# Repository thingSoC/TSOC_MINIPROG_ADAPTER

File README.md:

# TSOC_MINIPROG_ADAPTER

**TSOC_MINIPROG_ADAPTER** is a USB Serial, JTAG, and I2C programming adapter for thingSoc, 
and an example **thingSoC Reference Design.** 

[thingSoC](http://www.thingsoc.com) is an open source standard that defines a vendor 
independent socket system for the creation of new Internet Things with automatic configuration options. 
The [thingSoC](http://www.thingsoc.com) Default Programming Connector (DPC) is a sixteen(16) pin dual row type, with 254mm spacing,
and is compatible with what is refered to in the industry as the "FTDI Basic" connector. 
[thingSoC](http://www.thingsoc.com) supports a wide variety of programming interfaces, 
including JTAG/SWD, I2C, SPI, UART, and USB Serial, and the Default Programming Connector (DPC)
can support a number of simultaineous interfaces.

The **TSOC_MINIPROG_ADAPTER** facilitates the use of "FTDI" USB to UART Serial Adapters
like the [Sparkfun FTDI Basic Breakout](https://www.sparkfun.com/products/9873) for serial bootstrap programming.
The **TSOC_MINIPROG_ADAPTER** also facilitates the use of "MiniProg" programmers,
such as the [MiniProg3](http://www.cypress.com/documentation/development-kitsboards/cy8ckit-002-psoc-miniprog3-program-and-debug-kit), 
[MiniProg1](http://www.cypress.com/documentation/development-kitsboards/cy3217-miniprog1), and [PSoC3/4/5 KitProg](http://www.cypress.com/documentation/development-kitsboards/cy8ckit-059-psoc-5lp-prototyping-kit-onboard-programmer-and).

The **thingSoC Reference Designs** are example thingSoC implementations that implement
various reference and testing circuits for demonstrating the use of the thingSoC libraries.
These reference designs are complete designs and can also serve as starting templates for users to customize.

---------------------------------------

[ *TSOC_MINIPROG_ADAPTER Top*](https://github.com/thingSoC/) [ *TSOC_MINIPROG_ADAPTER Bottom*](https://github.com/thingSoC/)

* thingSoC Compliant Module
* thingSoC Default Programming Connector (thingSoc DPC)
* FTDI Connector Adapter
* Miniprog Connector Adapter
* ISSP/I2C Programmer Adapter

---------------------------------------

## Documentation Index <a name="documentation_index"/>

[thingSoC Organization Website](http://thingSoC.github.io)

[thingSoC FAQ - Frequently Asked Questions](http://thingsoc.github.io/support/faq.html)

---------------------------------------

[  
*thingSoC*](http://thingsoc.github.io)

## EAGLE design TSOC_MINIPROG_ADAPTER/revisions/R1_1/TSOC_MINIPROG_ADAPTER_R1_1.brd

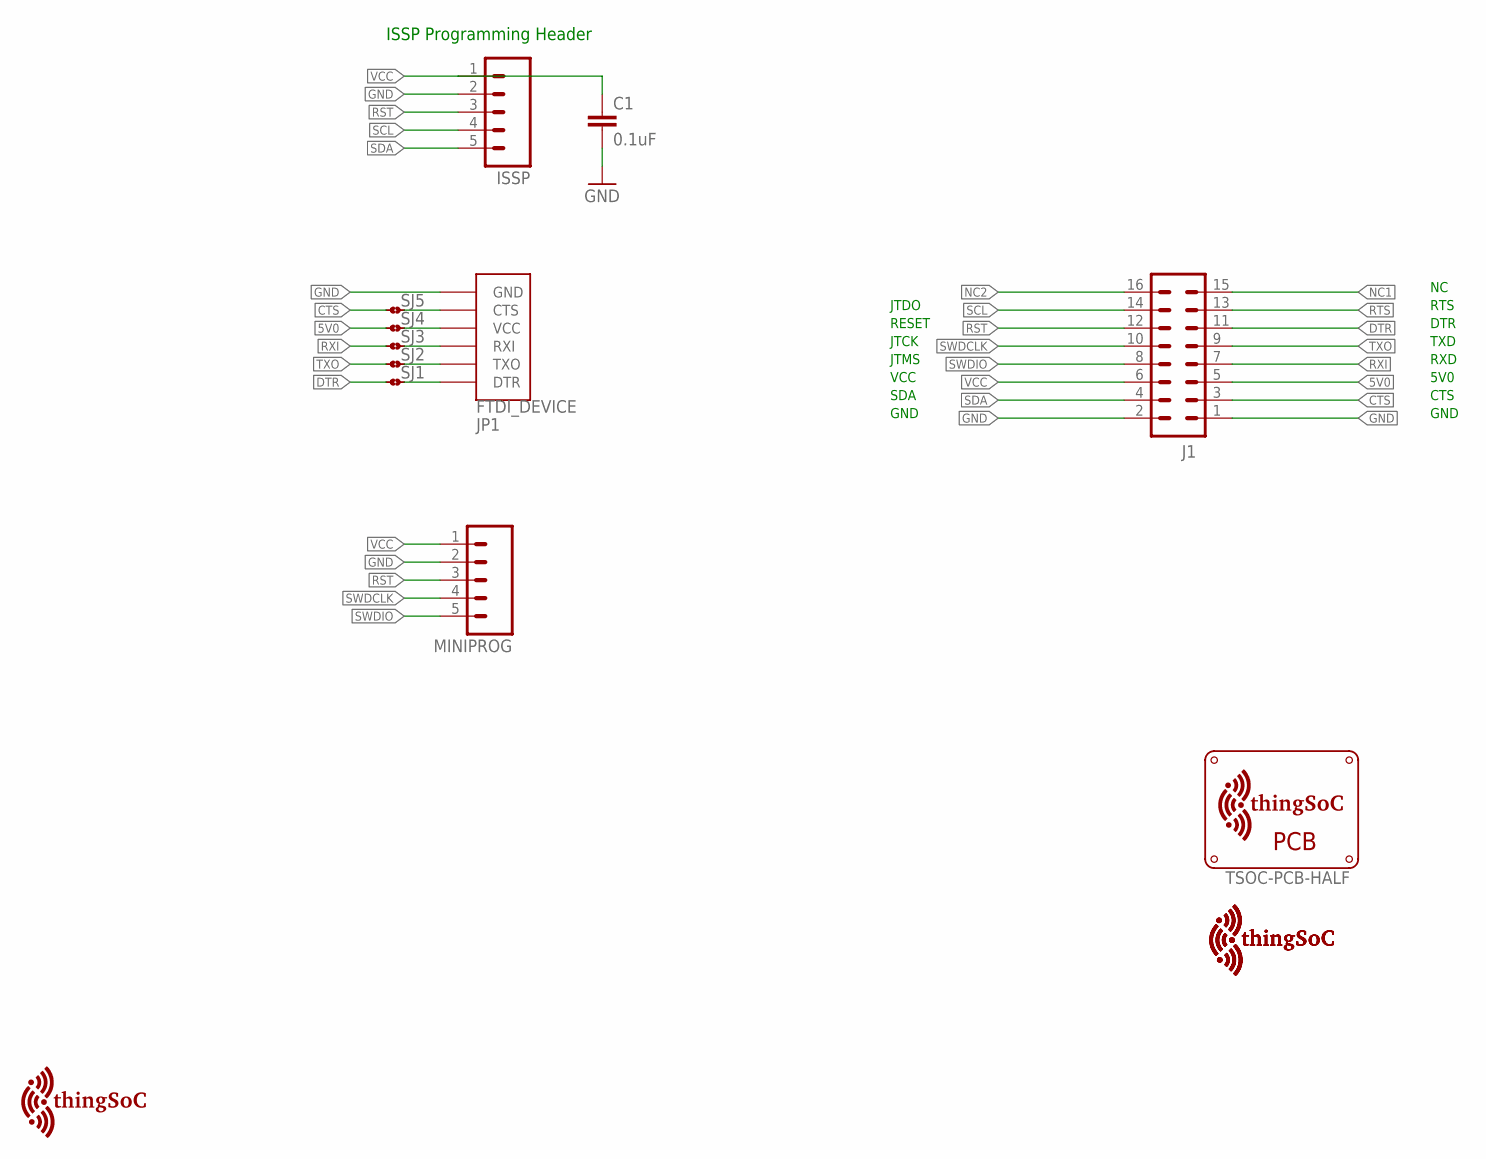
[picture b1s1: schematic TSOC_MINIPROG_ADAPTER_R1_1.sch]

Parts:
C1: 0.1uF; 0603-CAP
ISSP: M05PTH; 1X05
J1: M08X2; 2X8
JP1: FTDI_DEVICE; FTDI_DEVICE_SIDE
MINIPROG: M05PTH; 1X05
SJ1, SJ2, SJ3, SJ4, SJ5: JMP-2-NO
U$3, U$5: TSOC-LOGO-SMALL; TSOC-LOGO-SML
U$4: TSOC-PCB-HALF; TSOC-BB-BRD-HALF
U$6: TSOC-LOGO-LRG

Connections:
5V0: J1.5, SJ4.1
!CTS: J1.3, SJ5.1
!DTR: J1.11, SJ1.1
!RST: ISSP.3, J1.12, MINIPROG.3
!RTS: J1.13
FVCC: JP1.P$4 (VCC), SJ4.2
GND: C1.2, ISSP.2, J1.1, J1.2, JP1.P$6 (GND), MINIPROG.2
unnamed: JP1.P$1 (DTR), SJ1.2
unnamed: JP1.P$5 (CTS), SJ5.2
unnamed: JP1.P$3 (RXI), SJ3.2
unnamed: JP1.P$2 (TXO), SJ2.2
NC1: J1.15
NC2: J1.16
RXI: J1.7, SJ3.1
SCL: ISSP.4, J1.14
SDA: ISSP.5, J1.4
SWDCLK: J1.10, MINIPROG.4
SWDIO: J1.8, MINIPROG.5
TXO: J1.9, SJ2.1
VCC: C1.1, ISSP.1, J1.6, MINIPROG.1

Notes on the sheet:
RTS
DTR
RXD
TXD
CTS
5V0
GND
SDA
VCC
JTMS
JTCK
RESET
JTDO
ISSP Programming Header

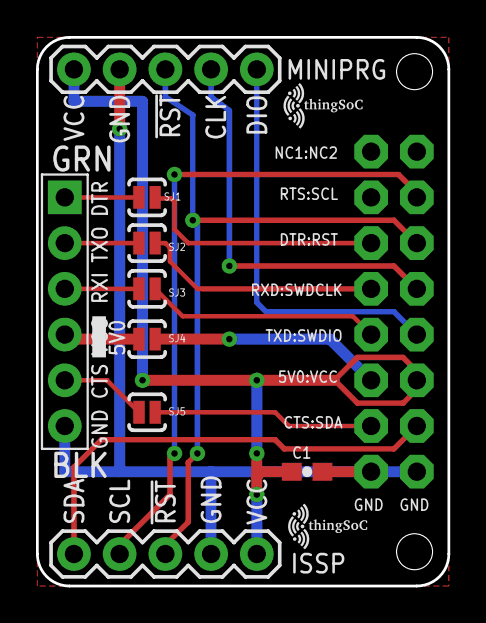
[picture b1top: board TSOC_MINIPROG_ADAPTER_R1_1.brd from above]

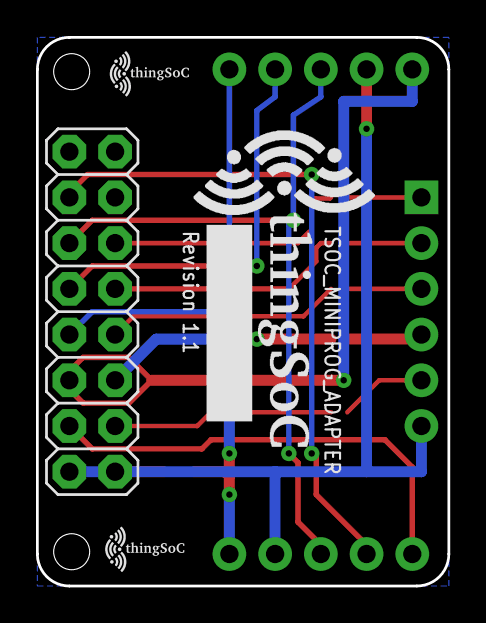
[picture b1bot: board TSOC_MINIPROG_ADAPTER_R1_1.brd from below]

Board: 2 copper layers, 22.9 x 30.5 mm, 16 parts (4 on the bottom side), 17 nets.

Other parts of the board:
U$1, U$2: TSOC-LOGO-SMALL; TSOC-LOGO-SML

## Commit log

2016-07-07 update to V1_0

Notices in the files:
parts and their libraries:
PatternAgents-ProtoPads: License : http://creativecommons.org/licenses/by-sa/4.0
(Creative Commons 4.0)
SparkFun-Connectors: Licensing: Creative Commons ShareAlike 4.0 International - https://creativecommons.org/licenses/by-sa/4.0
